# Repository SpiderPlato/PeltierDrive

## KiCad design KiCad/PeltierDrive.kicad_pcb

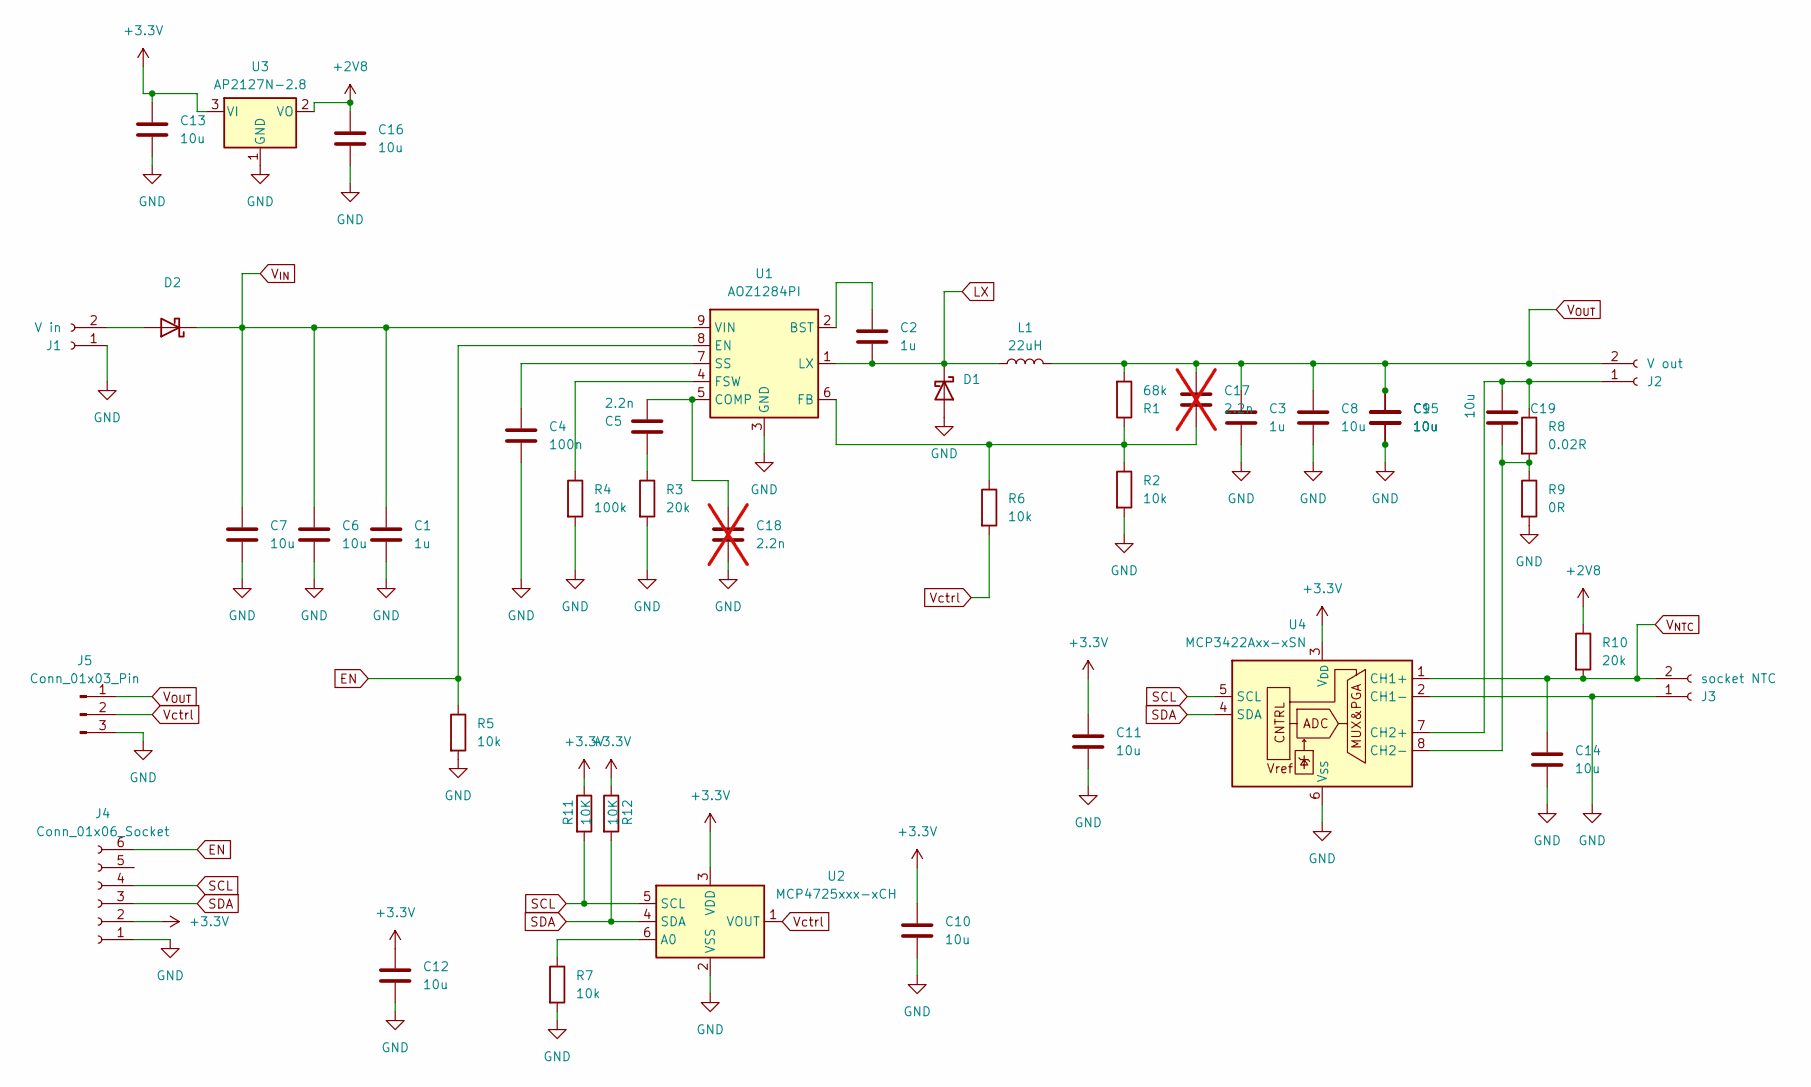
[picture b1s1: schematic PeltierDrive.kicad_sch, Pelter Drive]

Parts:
C1, C3: 1u; C_0805_2012Metric_Pad1.18x1.45mm_HandSolder
C2: 1u; C_0603_1608Metric_Pad1.08x0.95mm_HandSolder
C4: 100n; C_0805_2012Metric_Pad1.18x1.45mm_HandSolder
C5: 2.2n; C_0805_2012Metric_Pad1.18x1.45mm_HandSolder
C6, C7, C8, C9, C10, C11, C12, C13, C14, C15, C16, C19: 10u; C_0805_2012Metric_Pad1.18x1.45mm_HandSolder
C17: 2.2n; C_0603_1608Metric_Pad1.08x0.95mm_HandSolder; not fitted
C18: 2.2n; C_0805_2012Metric_Pad1.18x1.45mm_HandSolder; not fitted
D1, D2: PMEG3050CEP; D_SMA
J1: V in; TerminalBlock_MetzConnect_Type094_RT03502HBLU_1x02_P5.00mm_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
J2: V out; TerminalBlock_MetzConnect_Type094_RT03502HBLU_1x02_P5.00mm_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
J3: socket NTC; TerminalBlock_MetzConnect_Type094_RT03502HBLU_1x02_P5.00mm_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
J4: Conn_01x06_Socket; PinHeader_1x06_P2.54mm_Horizontal
J5: Conn_01x03_Pin; PinHeader_1x03_P2.54mm_Vertical
L1: 22uH; L_12x12mm_H8mm
R1: 68k; R_0603_1608Metric_Pad0.98x0.95mm_HandSolder
R2, R5, R6, R7: 10k; R_0603_1608Metric_Pad0.98x0.95mm_HandSolder
R3, R10: 20k; R_0603_1608Metric_Pad0.98x0.95mm_HandSolder
R4: 100k; R_0603_1608Metric_Pad0.98x0.95mm_HandSolder
R8: 0.02R; R_0805_2012Metric_Pad1.20x1.40mm_HandSolder
R9: 0R; R_0805_2012Metric_Pad1.20x1.40mm_HandSolder
R11, R12: 10K; R_0603_1608Metric_Pad0.98x0.95mm_HandSolder
U1: AOZ1284PI; SOIC-8-1EP_3.9x4.9mm_P1.27mm_EP2.71x3.7mm
U2: MCP4725xxx-xCH; SOT-23-6
U3: AP2127N-2.8; SOT-23
U4: MCP3422Axx-xSN; SOIC-8_3.9x4.9mm_P1.27mm

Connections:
+2V8: C16.1, R10.1, U3.2 (VO)
+3.3V: C10.1, C11.1, C12.1, C13.1, J4.2, R11.1, R12.1, U2.3 (VDD), U3.3 (VI), U4.3 (V_{DD})
EN: J4.6, R5.1, U1.8 (EN)
GND: C1.2, C3.2, C4.2, C6.2, C7.2, C8.2, C9.2, C10.2, C11.2, C12.2, C13.2, C14.2, C15.2, C16.2, C18.2, D1.2 (A), J1.1, J3.1, J4.1, J5.3, R2.2, R3.2, R4.2, R5.2, R7.2, R9.2, U1.3 (GND), U2.2 (VSS), U3.1 (GND), U4.2 (CH1-), U4.6 (V_{SS})
LX: C2.2, D1.1 (K), L1.1, U1.1 (LX)
unnamed: C5.2, R3.1
unnamed: D2.2 (A), J1.2
unnamed: C19.1, J2.1, R8.1, U4.7 (CH2+)
unnamed: C2.1, U1.2 (BST)
unnamed: C5.1, C18.1, U1.5 (COMP)
unnamed: C17.2, R1.1, R2.1, R6.1, U1.6 (FB)
unnamed: R4.1, U1.4 (FSW)
unnamed: C4.1, U1.7 (SS)
unnamed: R7.1, U2.6 (A0)
unnamed: C19.2, R8.2, R9.1, U4.8 (CH2-)
SCL: J4.4, R11.2, U2.5 (SCL), U4.5 (SCL)
SDA: J4.3, R12.2, U2.4 (SDA), U4.4 (SDA)
V_{IN}: C1.1, C6.1, C7.1, D2.1 (K), U1.9 (VIN)
V_{NTC}: C14.1, J3.2, R10.2, U4.1 (CH1+)
V_{OUT}: C3.1, C8.1, C9.1, C15.1, C17.1, J2.2, J5.1, L1.2, R1.2
Vctrl: J5.2, R6.2, U2.1 (VOUT)

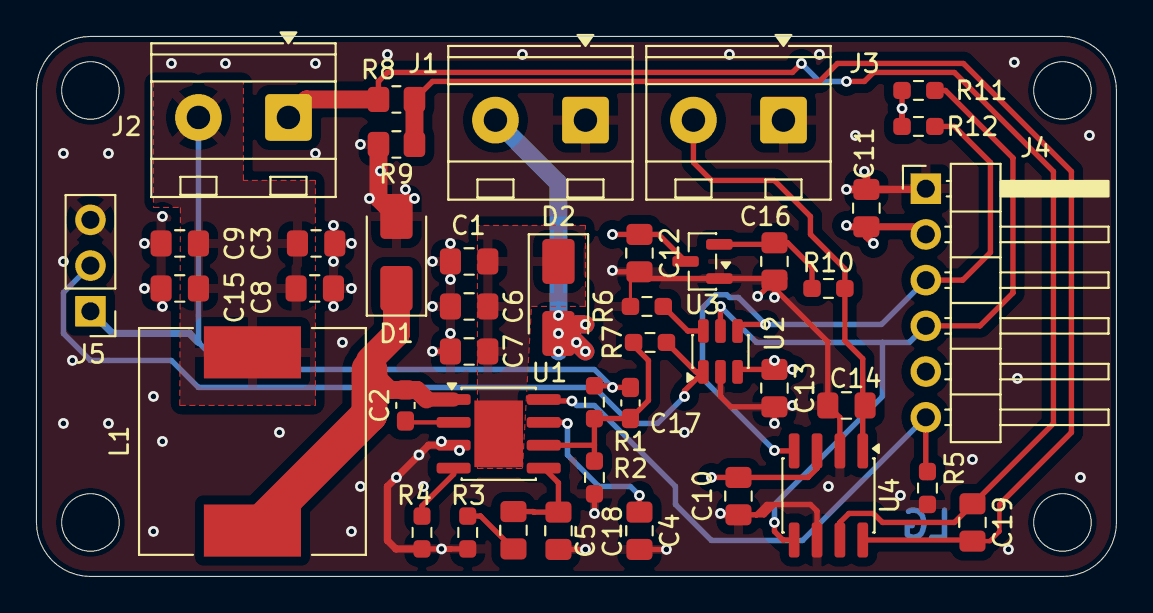
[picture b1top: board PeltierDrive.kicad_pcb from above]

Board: 4 copper layers, 60.0 x 30.0 mm, 43 parts (0 on the bottom side), 21 nets.

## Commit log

2026-02-18 schematic concept
2026-02-18 commponents placed roughly
2026-02-19 layout completed
2026-03-10 pushed PCB to manufacturing
2026-03-10 move KiCad files to subfolder
2026-03-10 add FW for RP2040 i uPython
2026-03-15 FW - adc and dac test
2026-03-30 first test with FB loop closed
2026-03-30 bom updats after the PCB assembly
